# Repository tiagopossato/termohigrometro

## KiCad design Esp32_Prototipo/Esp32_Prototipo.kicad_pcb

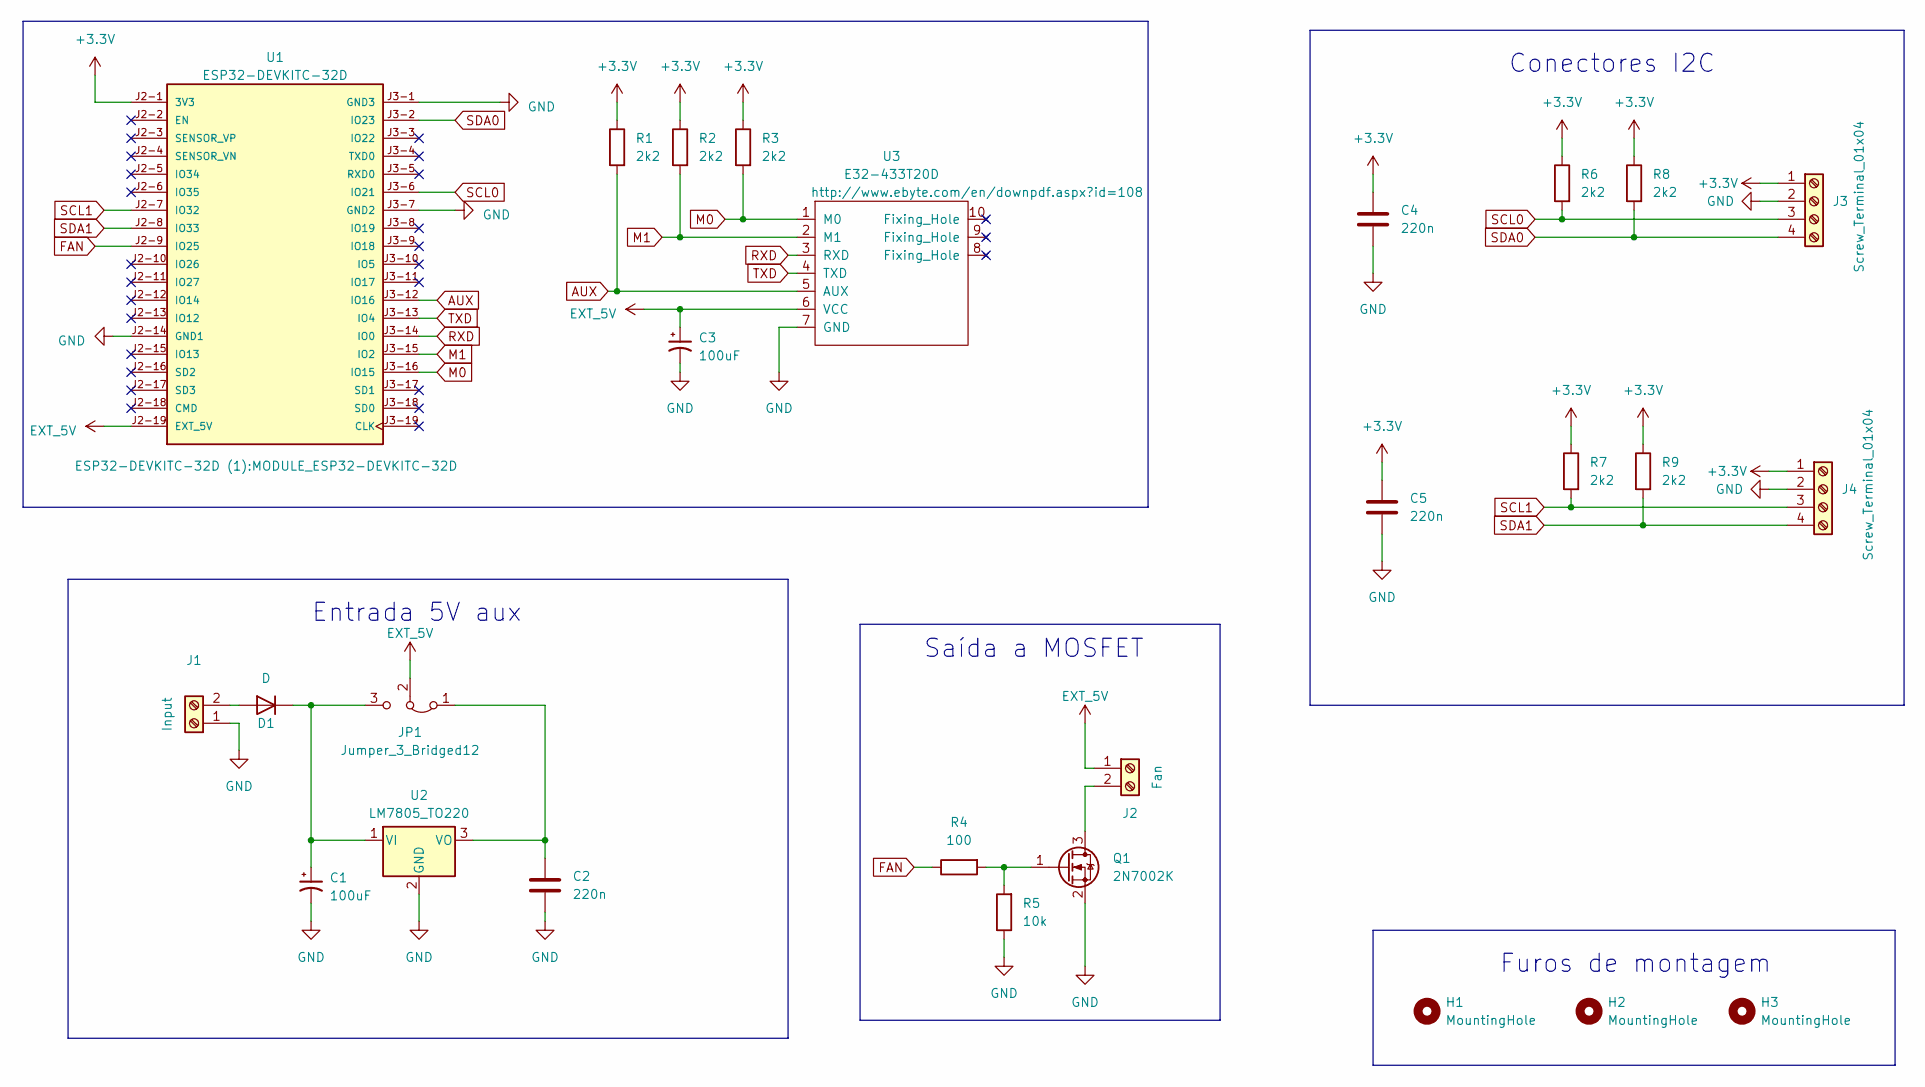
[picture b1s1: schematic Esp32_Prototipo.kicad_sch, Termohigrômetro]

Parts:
C1, C3: 100uF; CP_Radial_D6.3mm_P2.50mm
C2, C4, C5: 220n; C_Disc_D5.0mm_W2.5mm_P5.00mm
D1: D; D_DO-41_SOD81_P7.62mm_Horizontal
H1, H2, H3: MountingHole; MountingHole_3.2mm_M3
J1: Input; TerminalBlock_4Ucon_1x02_P3.50mm_Horizontal
J2: Fan; TerminalBlock_4Ucon_1x02_P3.50mm_Horizontal
J3, J4: Screw_Terminal_01x04; TerminalBlock_4Ucon_1x04_P3.50mm_Horizontal
JP1: Jumper_3_Bridged12; PinHeader_1x03_P2.54mm_Vertical
Q1: 2N7002K; SOT-23
R1, R2, R3, R6, R7, R8, R9: 2k2; R_Axial_DIN0207_L6.3mm_D2.5mm_P10.16mm_Horizontal
R4: 100; R_Axial_DIN0207_L6.3mm_D2.5mm_P10.16mm_Horizontal
R5: 10k; R_Axial_DIN0207_L6.3mm_D2.5mm_P10.16mm_Horizontal
U1: ESP32-DEVKITC-32D; MODULE_ESP32-DEVKITC-32D; PARTREV V4
U2: LM7805_TO220; TO-220-3_Vertical
U3: E32-433T20D; E32-xxxT20D

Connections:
+3V3: C4.2, C5.2, J3.1, J4.1, R1.1, R2.1, R3.1, R6.1, R7.1, R8.1, R9.1, U1.J2-1 (3V3)
+BATT: C3.1, J2.1, JP1.2 (C), U1.J2-19 (EXT_5V), U3.6 (VCC)
AUX: R1.2, U1.J3-12 (IO16), U3.5 (AUX)
FAN: R4.1, U1.J2-9 (IO25)
GND: C1.2, C2.1, C3.2, C4.1, C5.1, J1.1, J3.2, J4.2, Q1.2 (S), R5.1, U1.J2-14 (GND1), U1.J3-1 (GND3), U1.J3-7 (GND2), U2.2 (GND), U3.7 (GND)
M0: R3.2, U1.J3-16 (IO15), U3.1 (M0)
M1: R2.2, U1.J3-15 (IO2), U3.2 (M1)
unnamed: D1.2 (A), J1.2
unnamed: C1.1, D1.1 (K), JP1.3 (B), U2.1 (VI)
unnamed: J2.2, Q1.3 (D)
unnamed: C2.2, JP1.1 (A), U2.3 (VO)
unnamed: Q1.1 (G), R4.2, R5.2
RXD: U1.J3-14 (IO0), U3.3 (RXD)
SCL0: J3.3, R6.2, U1.J3-6 (IO21)
SCL1: J4.3, R7.2, U1.J2-7 (IO32)
SDA0: J3.4, R8.2, U1.J3-2 (IO23)
SDA1: J4.4, R9.2, U1.J2-8 (IO33)
TXD: U1.J3-13 (IO4), U3.4 (TXD)

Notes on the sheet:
Conectores I2C
Saída a MOSFET
Entrada 5V aux
Furos de montagem

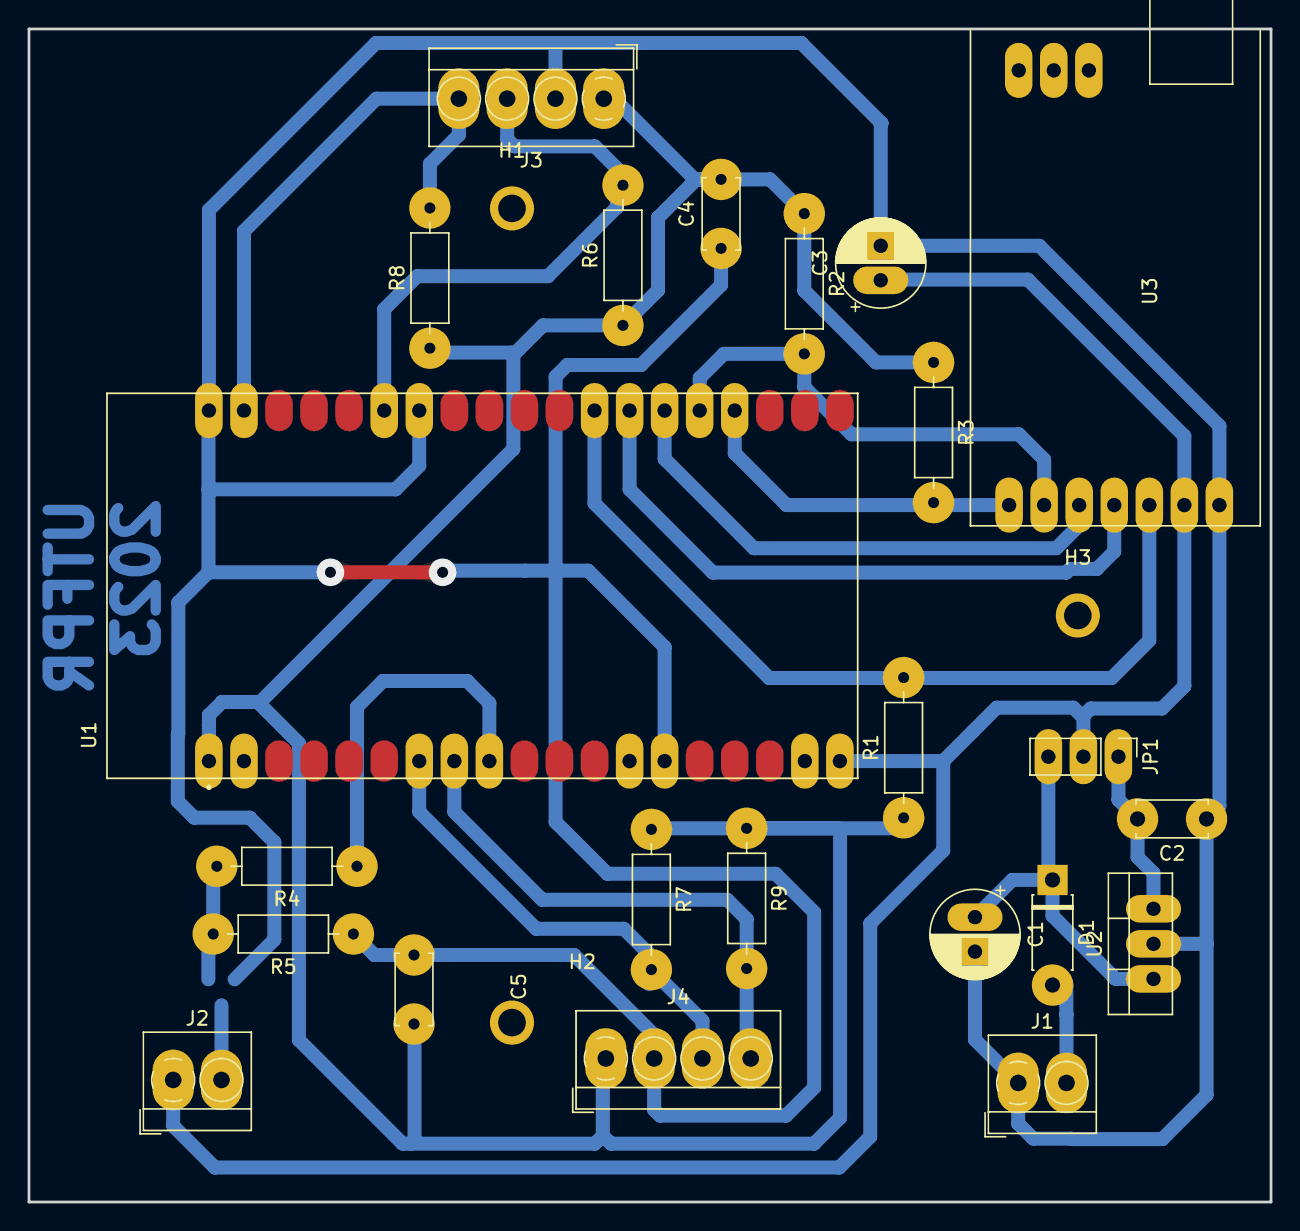
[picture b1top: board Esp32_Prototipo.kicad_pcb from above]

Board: 2 copper layers, 90.0 x 85.0 mm, 27 parts (1 on the bottom side), 18 nets.

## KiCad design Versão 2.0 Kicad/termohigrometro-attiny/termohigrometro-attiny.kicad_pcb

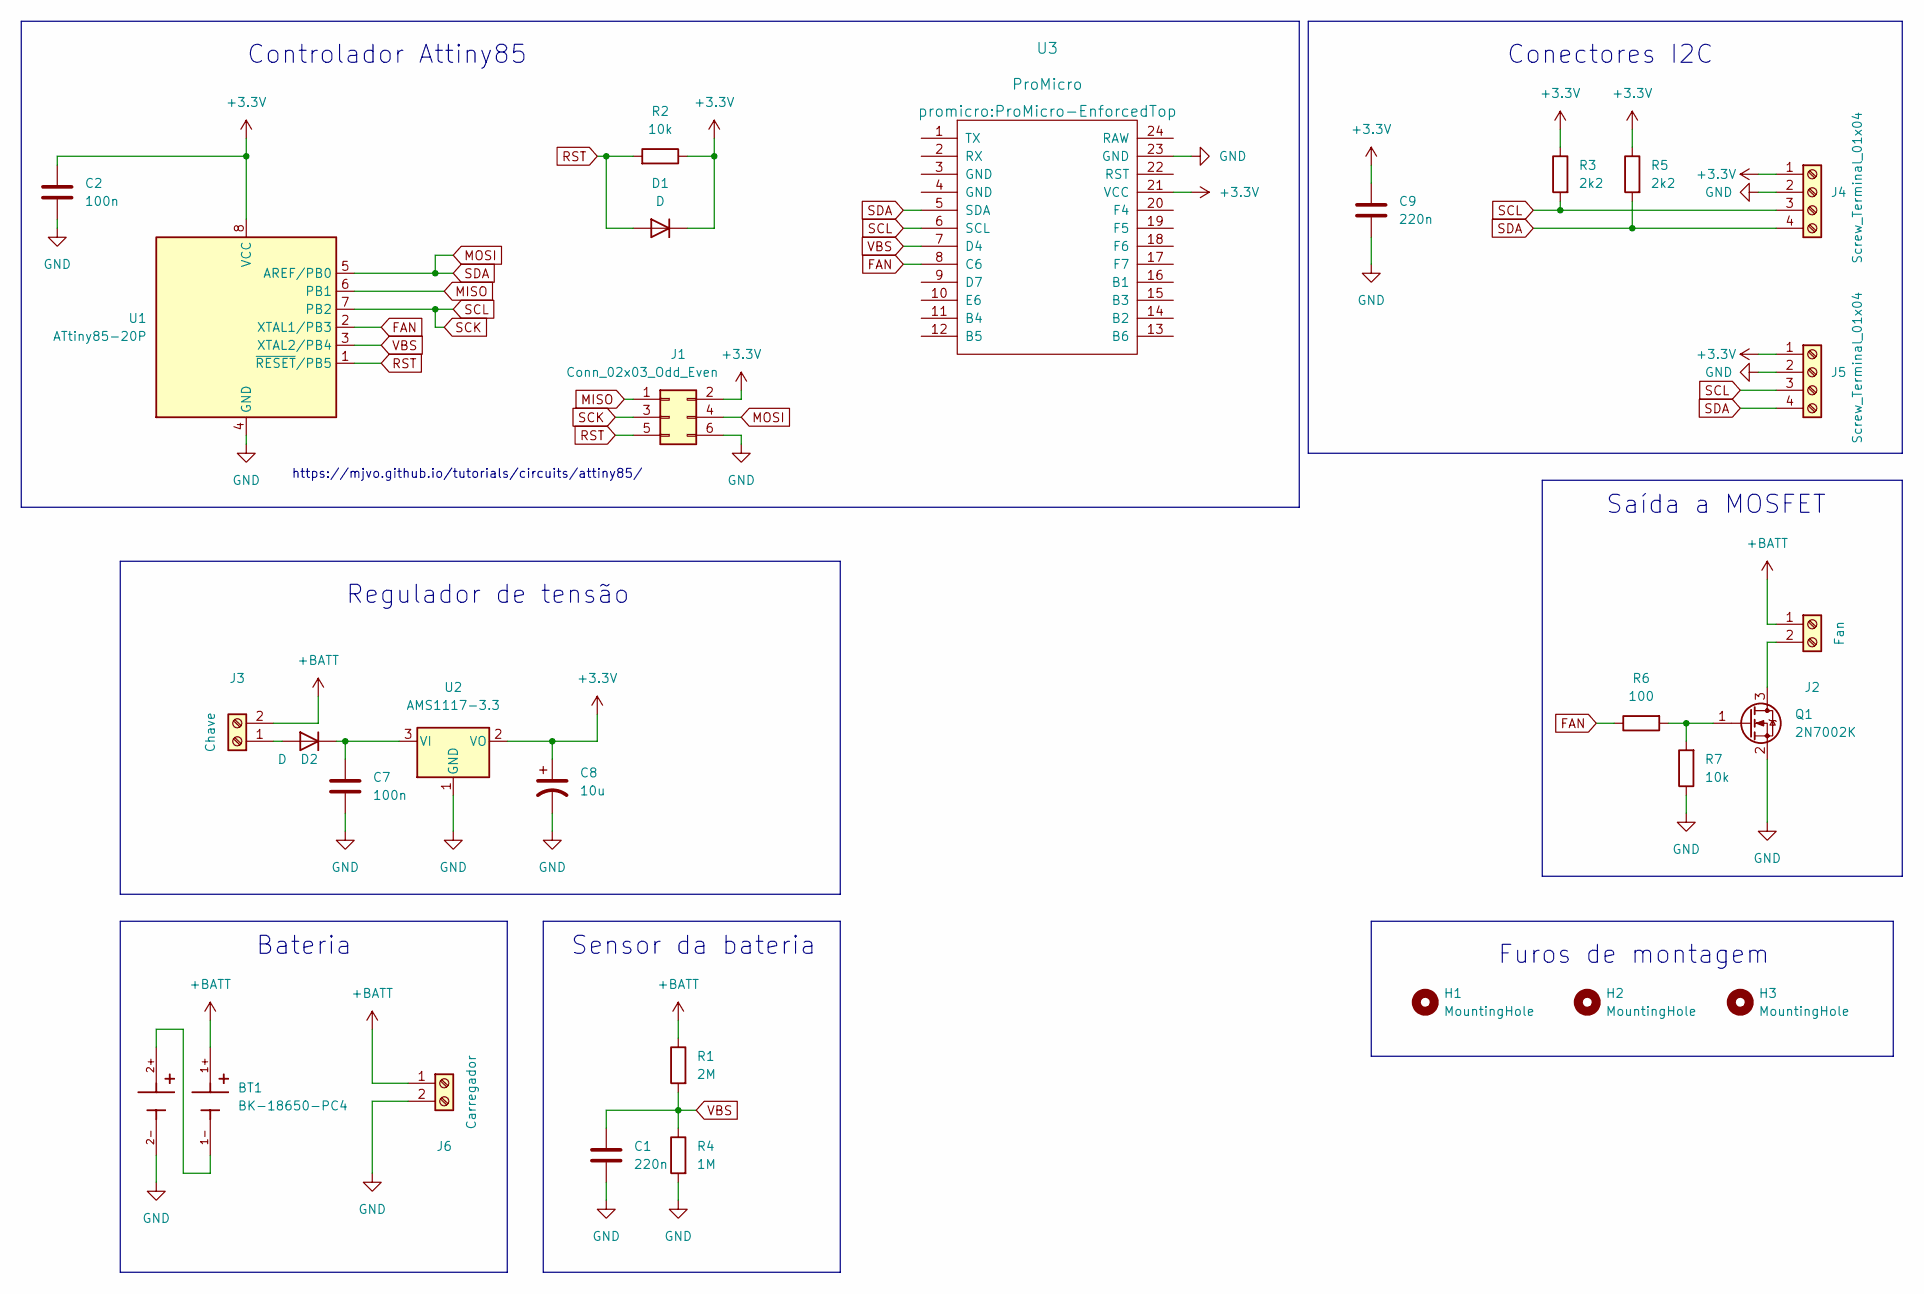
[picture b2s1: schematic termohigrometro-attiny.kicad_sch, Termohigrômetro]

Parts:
BT1: BK-18650-PC4; BAT_BK-18650-PC4; PARTREV K
C1, C9: 220n; C_Disc_D5.0mm_W2.5mm_P5.00mm
C2, C7: 100n; C_Disc_D5.0mm_W2.5mm_P5.00mm
C8: 10u; CP_Radial_D6.3mm_P2.50mm
D1, D2: D; D_DO-41_SOD81_P7.62mm_Horizontal
H1, H2, H3: MountingHole; MountingHole_3.2mm_M3
J1: Conn_02x03_Odd_Even; PinHeader_2x03_P2.54mm_Vertical
J2: Fan; TerminalBlock_4Ucon_1x02_P3.50mm_Horizontal
J3: Chave; TerminalBlock_4Ucon_1x02_P3.50mm_Horizontal
J4, J5: Screw_Terminal_01x04; TerminalBlock_4Ucon_1x04_P3.50mm_Horizontal
J6: Carregador; TerminalBlock_4Ucon_1x02_P3.50mm_Horizontal
Q1: 2N7002K; SOT-23
R1: 2M; R_Axial_DIN0207_L6.3mm_D2.5mm_P10.16mm_Horizontal
R2: 10k; R_Axial_DIN0207_L6.3mm_D2.5mm_P10.16mm_Horizontal
R3, R5: 2k2; R_Axial_DIN0207_L6.3mm_D2.5mm_P10.16mm_Horizontal
R4: 1M; R_Axial_DIN0207_L6.3mm_D2.5mm_P10.16mm_Horizontal
R6: 100; R_Axial_DIN0207_L6.3mm_D2.5mm_P10.16mm_Horizontal
R7: 10k; R_0805_2012Metric
U1: ATtiny85-20P; DIP-8_W7.62mm
U2: AMS1117-3.3; SOT-223-3_TabPin2
U3: ProMicro; ProMicro-EnforcedTop

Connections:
+3V3: C2.1, C8.1, C9.2, D1.1 (K), J1.2, J4.1, J5.1, R2.1, R3.1, R5.1, U1.8 (VCC), U2.2 (VO), U3.21 (VCC)
+BATT: BT1.1+, J2.1, J3.2, J6.1, R1.1
FAN: R6.1, U1.2 (XTAL1/PB3), U3.8 (C6)
GND: BT1.2-, C1.1, C2.2, C7.1, C8.2, C9.1, J1.6, J4.2, J5.2, J6.2, Q1.2 (S), R4.2, R7.1, U1.4 (GND), U2.1 (GND), U3.23 (GND)
MISO: J1.1, U1.6 (PB1)
MOSI: J1.4, J4.4, J5.4, R5.2, U1.5 (AREF/PB0), U3.5 (SDA)
unnamed: BT1.1-, BT1.2+
unnamed: C7.2, D2.1 (K), U2.3 (VI)
unnamed: J2.2, Q1.3 (D)
unnamed: D2.2 (A), J3.1
unnamed: Q1.1 (G), R6.2, R7.2
RST: D1.2 (A), J1.5, R2.2, U1.1 (~RESET/PB5)
SCK: J1.3, J4.3, J5.3, R3.2, U1.7 (PB2), U3.6 (SCL)
VBS: C1.2, R1.2, R4.1, U1.3 (XTAL2/PB4), U3.7 (D4)

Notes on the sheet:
https://mjvo.github.io/tutorials/circuits/attiny85/
Conectores I2C
Sensor da bateria
Regulador de tensão
Saída a MOSFET
Furos de montagem
Bateria
Controlador Attiny85

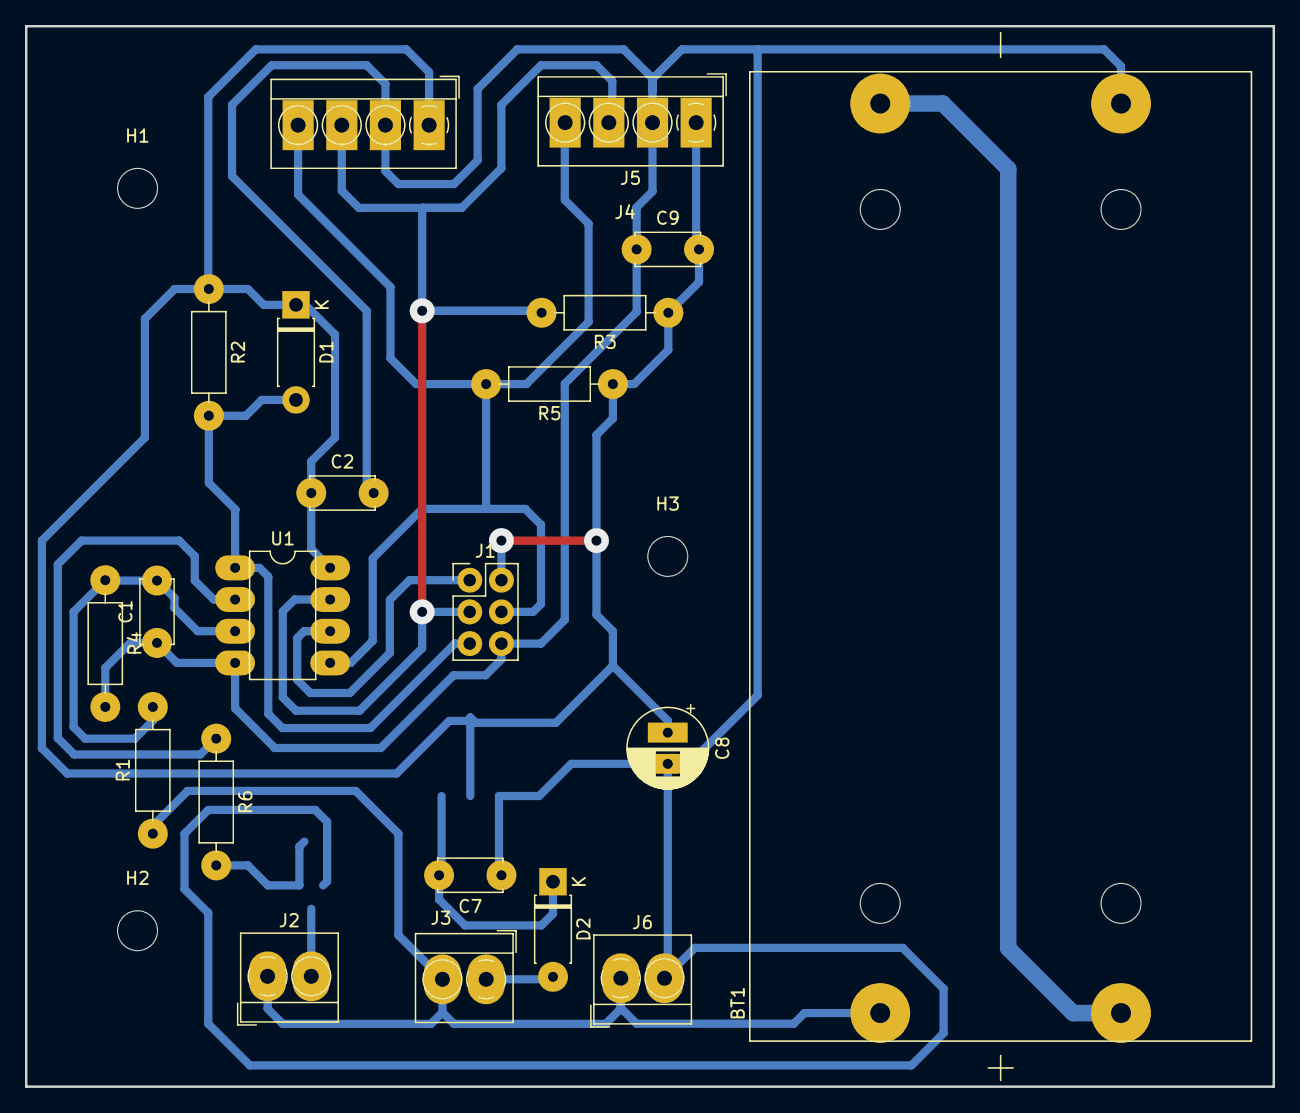
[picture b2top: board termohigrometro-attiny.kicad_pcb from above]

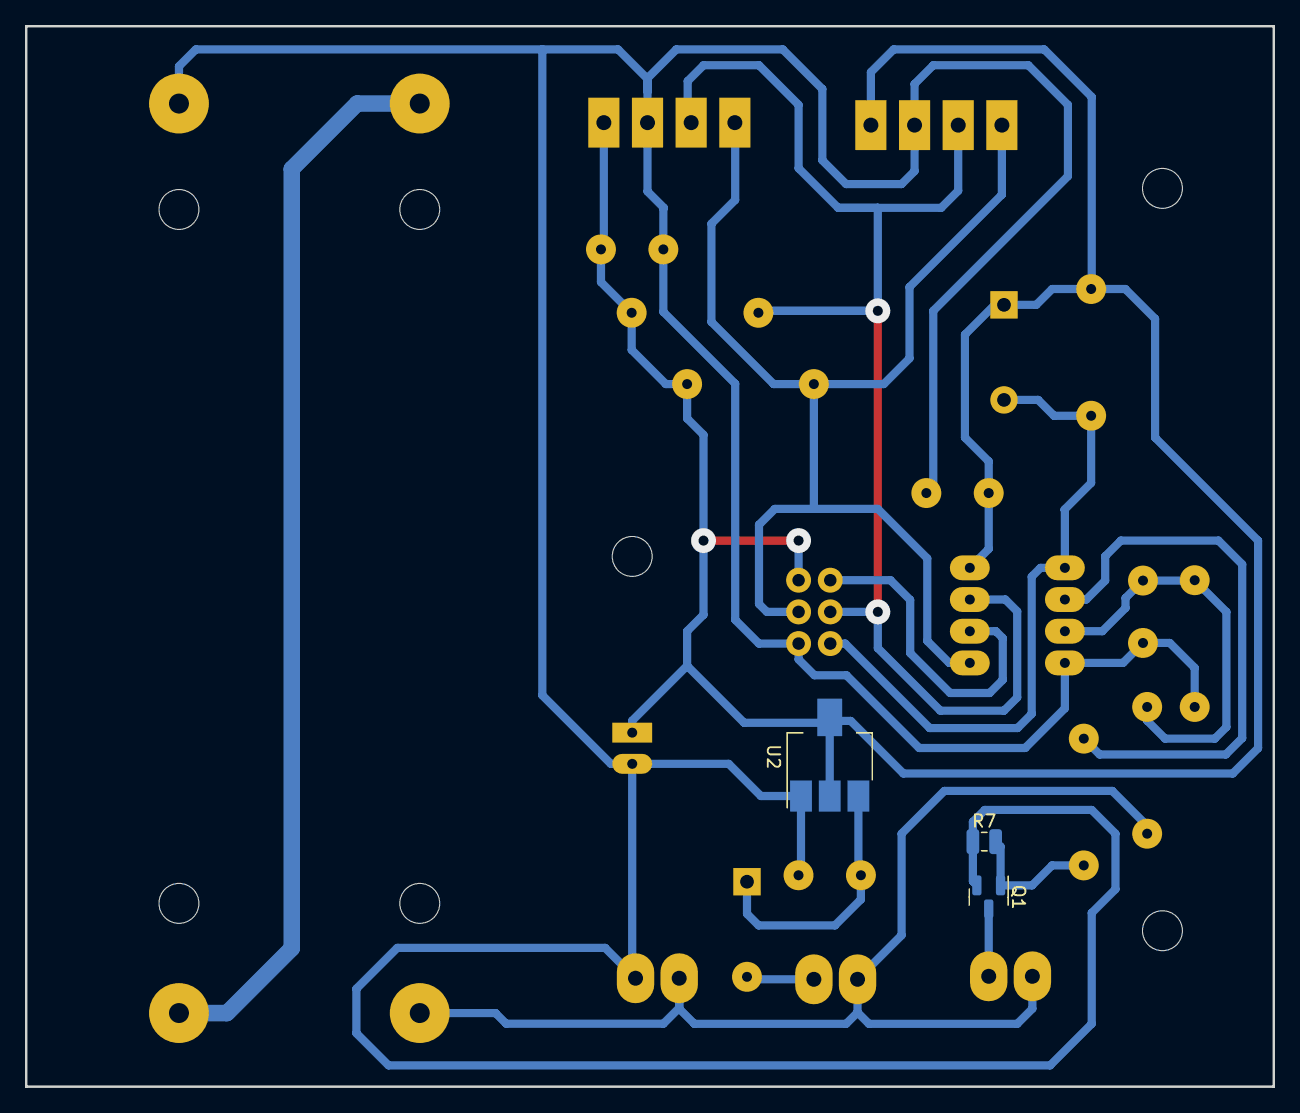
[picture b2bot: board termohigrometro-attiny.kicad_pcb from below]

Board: 2 copper layers, 100.0 x 85.0 mm, 27 parts (3 on the bottom side), 14 nets.

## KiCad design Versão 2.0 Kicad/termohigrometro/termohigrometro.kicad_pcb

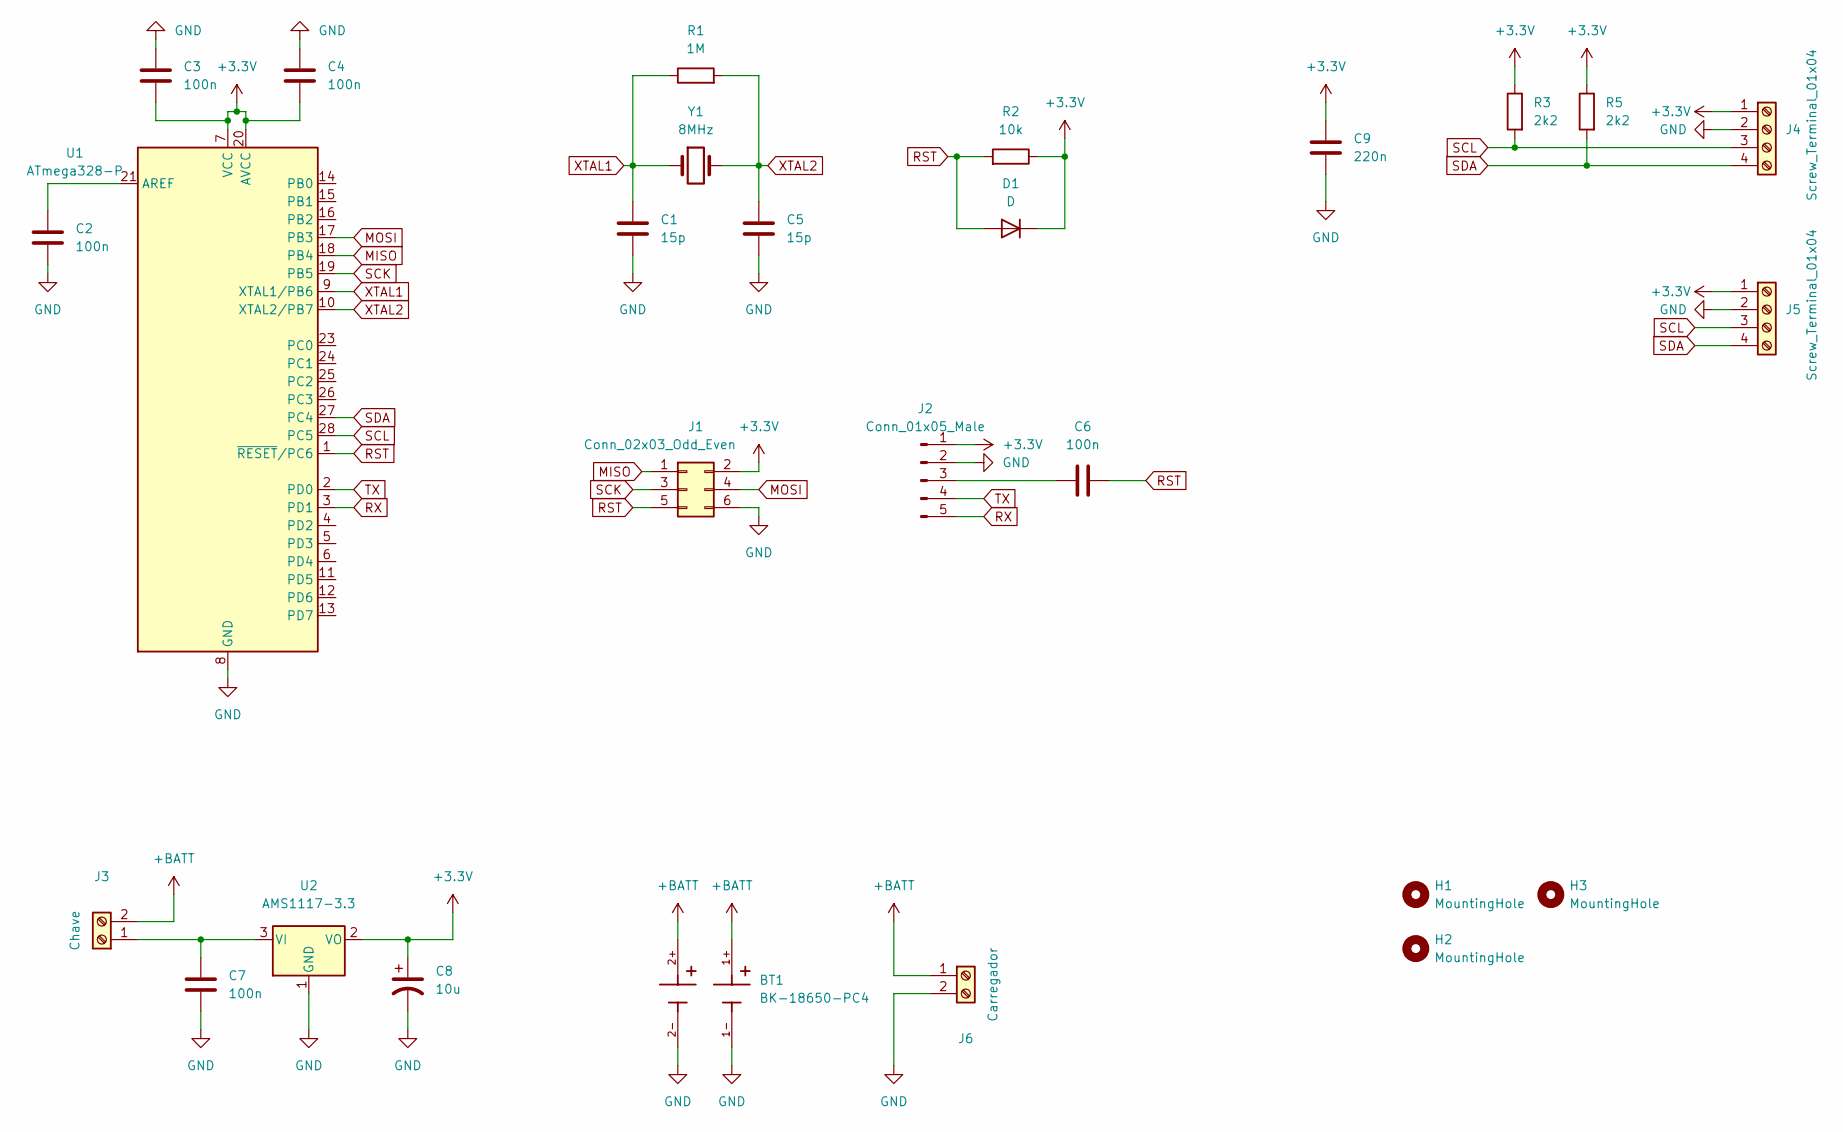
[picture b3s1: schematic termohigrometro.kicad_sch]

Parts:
BT1: BK-18650-PC4; BAT_BK-18650-PC4; PARTREV K
C1, C5: 15p; C_Disc_D5.0mm_W2.5mm_P5.00mm
C2, C3, C4, C6, C7: 100n; C_Disc_D5.0mm_W2.5mm_P5.00mm
C8: 10u; CP_Radial_D6.3mm_P2.50mm
C9: 220n; C_Disc_D5.0mm_W2.5mm_P5.00mm
D1: D; D_DO-41_SOD81_P7.62mm_Horizontal
H1, H2, H3: MountingHole; MountingHole_3.2mm_M3
J1: Conn_02x03_Odd_Even; PinHeader_2x03_P2.54mm_Vertical
J2: Conn_01x05_Male; PinHeader_1x05_P2.54mm_Vertical
J3: Chave; TerminalBlock_4Ucon_1x02_P3.50mm_Horizontal
J4, J5: Screw_Terminal_01x04; TerminalBlock_4Ucon_1x04_P3.50mm_Horizontal
J6: Carregador; TerminalBlock_4Ucon_1x02_P3.50mm_Horizontal
R1: 1M; R_Axial_DIN0207_L6.3mm_D2.5mm_P10.16mm_Horizontal
R2: 10k; R_Axial_DIN0207_L6.3mm_D2.5mm_P10.16mm_Horizontal
R3, R5: 2k2; R_Axial_DIN0207_L6.3mm_D2.5mm_P10.16mm_Horizontal
U1: ATmega328-P; DIP-28_W7.62mm_LongPads
U2: AMS1117-3.3; SOT-223-3_TabPin2
Y1: 8MHz; Crystal_HC49-4H_Vertical

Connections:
+3V3: C3.2, C4.2, C8.1, C9.2, D1.1 (K), J1.2, J2.1, J4.1, J5.1, R2.1, R3.1, R5.1, U1.7 (VCC), U1.20 (AVCC), U2.2 (VO)
+BATT: BT1.1+, BT1.2+, J3.2, J6.1
GND: BT1.1-, BT1.2-, C1.2, C2.2, C3.1, C4.1, C5.2, C7.1, C8.2, C9.1, J1.6, J2.2, J4.2, J5.2, J6.2, U1.8 (GND), U1.22 (GND), U2.1 (GND)
MISO: J1.1, U1.18 (PB4)
MOSI: J1.4, U1.17 (PB3)
unnamed: C2.1, U1.21 (AREF)
unnamed: C6.1, J2.3
unnamed: C7.2, J3.1, U2.3 (VI)
RST: C6.2, D1.2 (A), J1.5, R2.2, U1.1 (~RESET/PC6)
RX: J2.5, U1.3 (PD1)
SCK: J1.3, U1.19 (PB5)
SCL: J4.3, J5.3, R3.2, U1.28 (PC5)
SDA: J4.4, J5.4, R5.2, U1.27 (PC4)
TX: J2.4, U1.2 (PD0)
XTAL1: C1.1, R1.1, U1.9 (XTAL1/PB6), Y1.1
XTAL2: C5.1, R1.2, U1.10 (XTAL2/PB7), Y1.2

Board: 2 copper layers, 27 parts (1 on the bottom side), 16 nets, no tracks yet.

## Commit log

2017-09-13 Versao inicial
2022-12-18 organizando
2022-12-28 add atttiny project
2022-12-28 placa com attiny
2023-02-12 adicionado capacitor na leitura de tensão. Alterado ligação da bateria
2023-02-20 ADD ESP32
2023-02-22 proto esp32 pronto para montar
2023-02-22 add schmeatinc in pdf
2023-02-22 corrigido falha no schematico e alargado as trilhas
2025-07-13 adicionando codigo base para o termohigrometro da IDR
2025-07-13 acertando posição do texto
2025-07-16 funcionando
